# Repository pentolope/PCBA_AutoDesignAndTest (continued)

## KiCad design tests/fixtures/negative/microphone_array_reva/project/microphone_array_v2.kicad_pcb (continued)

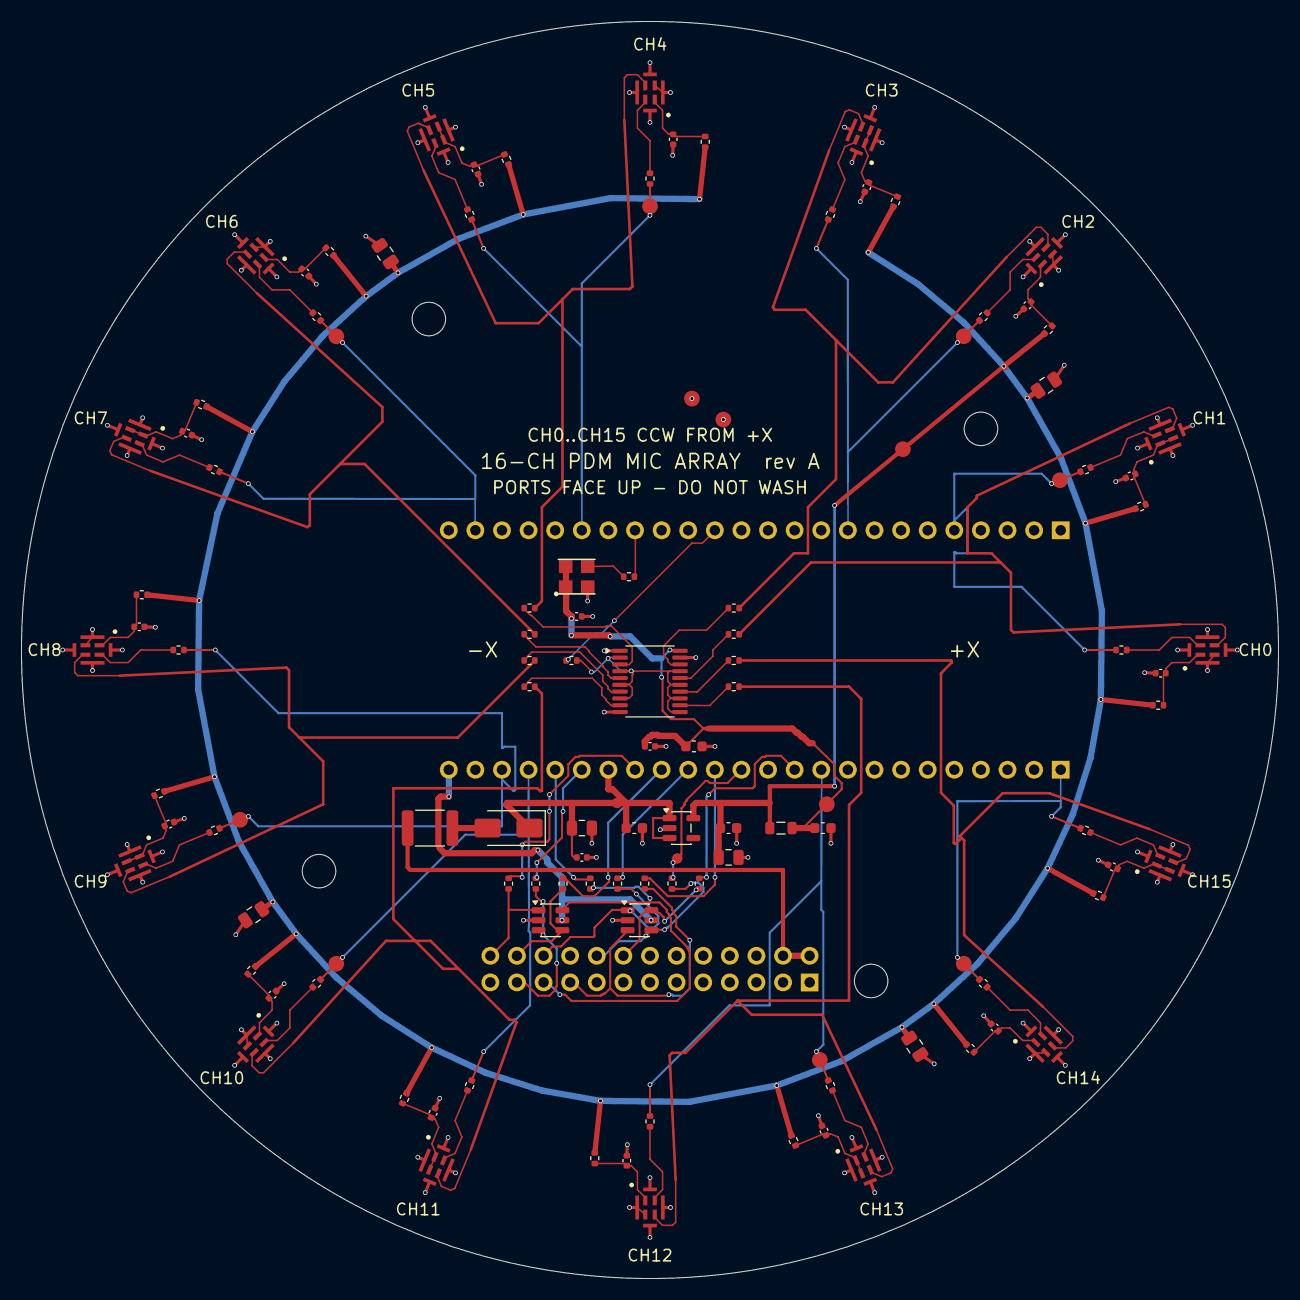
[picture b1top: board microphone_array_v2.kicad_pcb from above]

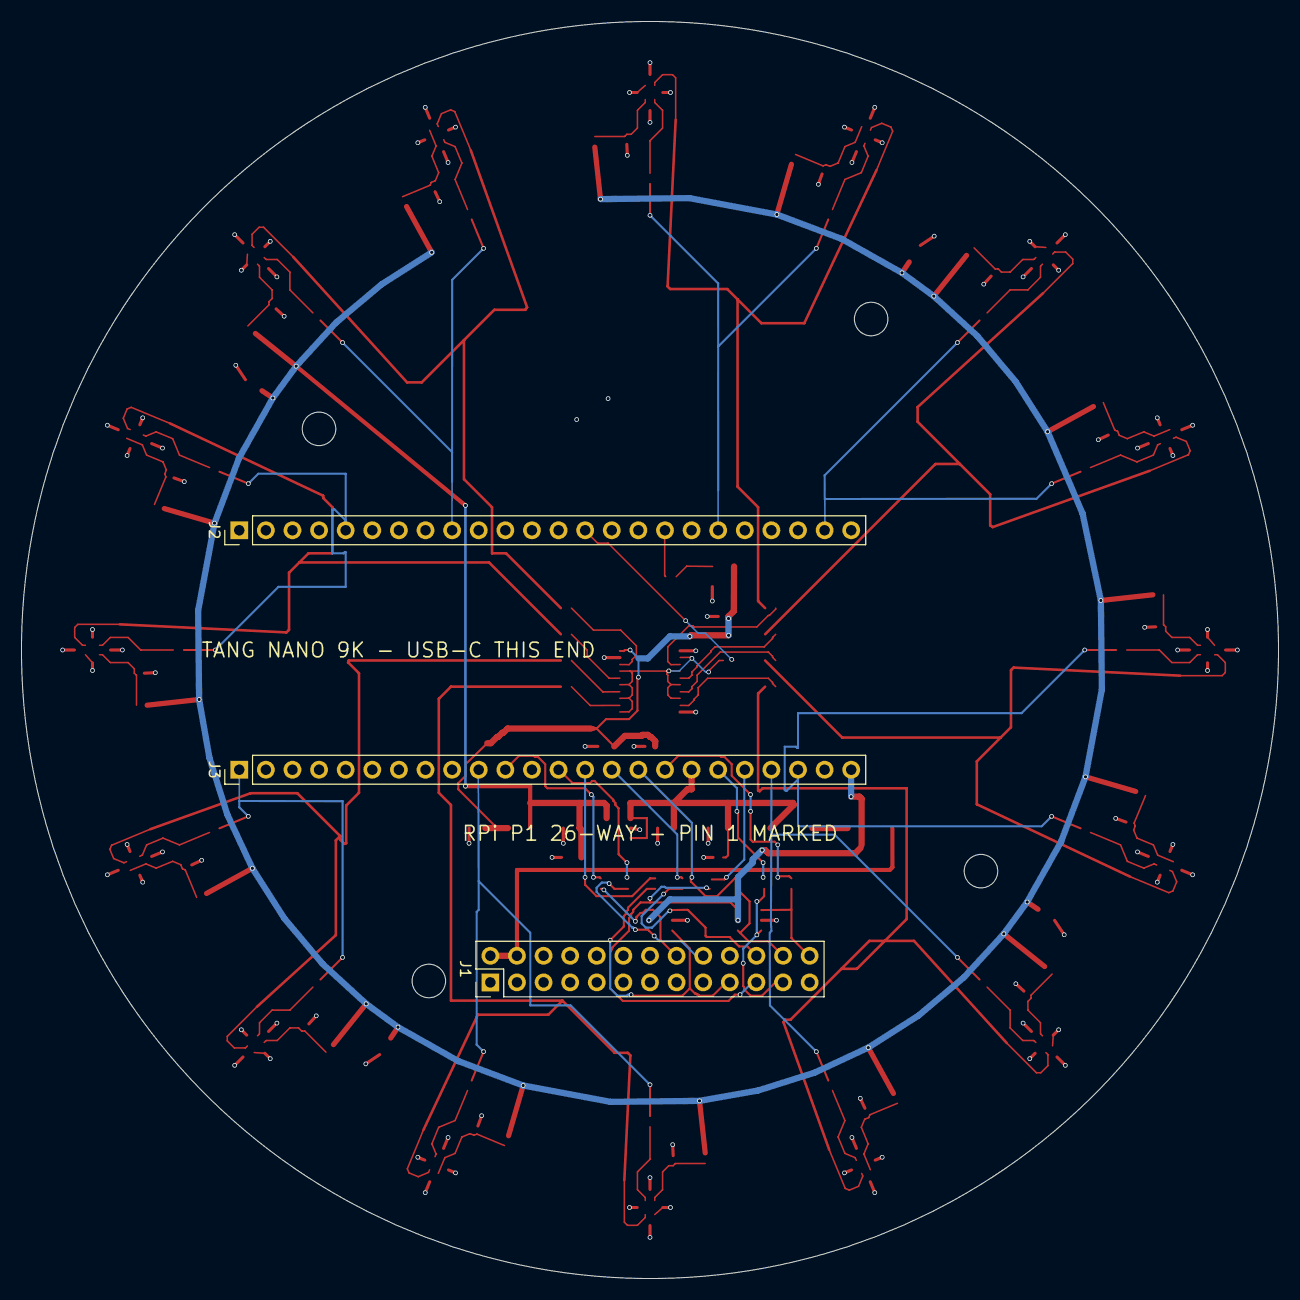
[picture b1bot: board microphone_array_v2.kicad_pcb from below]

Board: 4 copper layers, 120.0 x 120.0 mm, 124 parts (3 on the bottom side), 83 nets.
